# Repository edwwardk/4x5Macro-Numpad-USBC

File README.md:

## 4x5Macro-Numpad-USBC
This fork of tobychui's 4x5Macro-Numpad modifies the original design to use usbc instead of microusb as well as using a through hole reinforced port for a stronger hold on the board. Additionally, it also moves the user led to the front of the board and adds a button for resetting the mcu. Pins are identical to the 4x5Macro-Numpad to allow for using the same firmwares.

## v1.0 Known Issues
- resistor/capacitor/led designators/value missing from silkscreen in gerbers
- switch indices missing from silkscreen in gerbers
- size is larger than 100x100mm which causes upcharge (at least from jlcpcb)

### Bill of materials
(LCSC manufacturer part numbers in brackets)
- 1x CH552G (CH552G)
- 1x USBC (GT-USB-7010ASV)
- 20x switches for 4x5 layout, 17x switches for numpad layout
- 2x 0.1u 0805 capacitors (0805B104J250CT)
- 2x 0805 LEDs (17-215SURC/S530-A3/4T and BL-HJC35A-AV-TRB)
- 8x 10k 0805 resistors (SCR0805F10K)
- 2x 5.1k 0805 resistors (CR0805J80512G)
- 2x smd momentary buttons (TS5216A 250gf 025)

### Fabrication instructions
- in the "4x5Macro-Numpad-USBC/fabrication" folder there is a zip file called fabrication.zip. these are the set of gerbers required to order from JLCPCB and should work as is.

### Build Instruction

1. Send the PCB to print (See /PCB)

2. Purchase all the required materials (See BOM list)

3. 3D print the base plate (See /3D Model)

4. Install the required Arduino library for CH552G and drivers

5. Visit [4-key Macropad | imuslab](https://tobychui.github.io/4xMacropad/) (4xMacropad only) or modify the sketch in /firmware folder

6. Flash the CH552G with the sketch

### Program Flashing Instructions

As all the keyboard designs share the same MCU and programming button design, this instruction should be suitable for all the macropads / numpad in this repo.

1. Hold and press the PROG button on the PCB

2. While the button has been held, insert the USB cable into the mini USB port

3. Release the button when the Arduino code has finished compiling and ready to upload (Timing is important)

4. Wait for the upload to complete

### License

Software: MIT License

Hardware: CC BY-NC-SA

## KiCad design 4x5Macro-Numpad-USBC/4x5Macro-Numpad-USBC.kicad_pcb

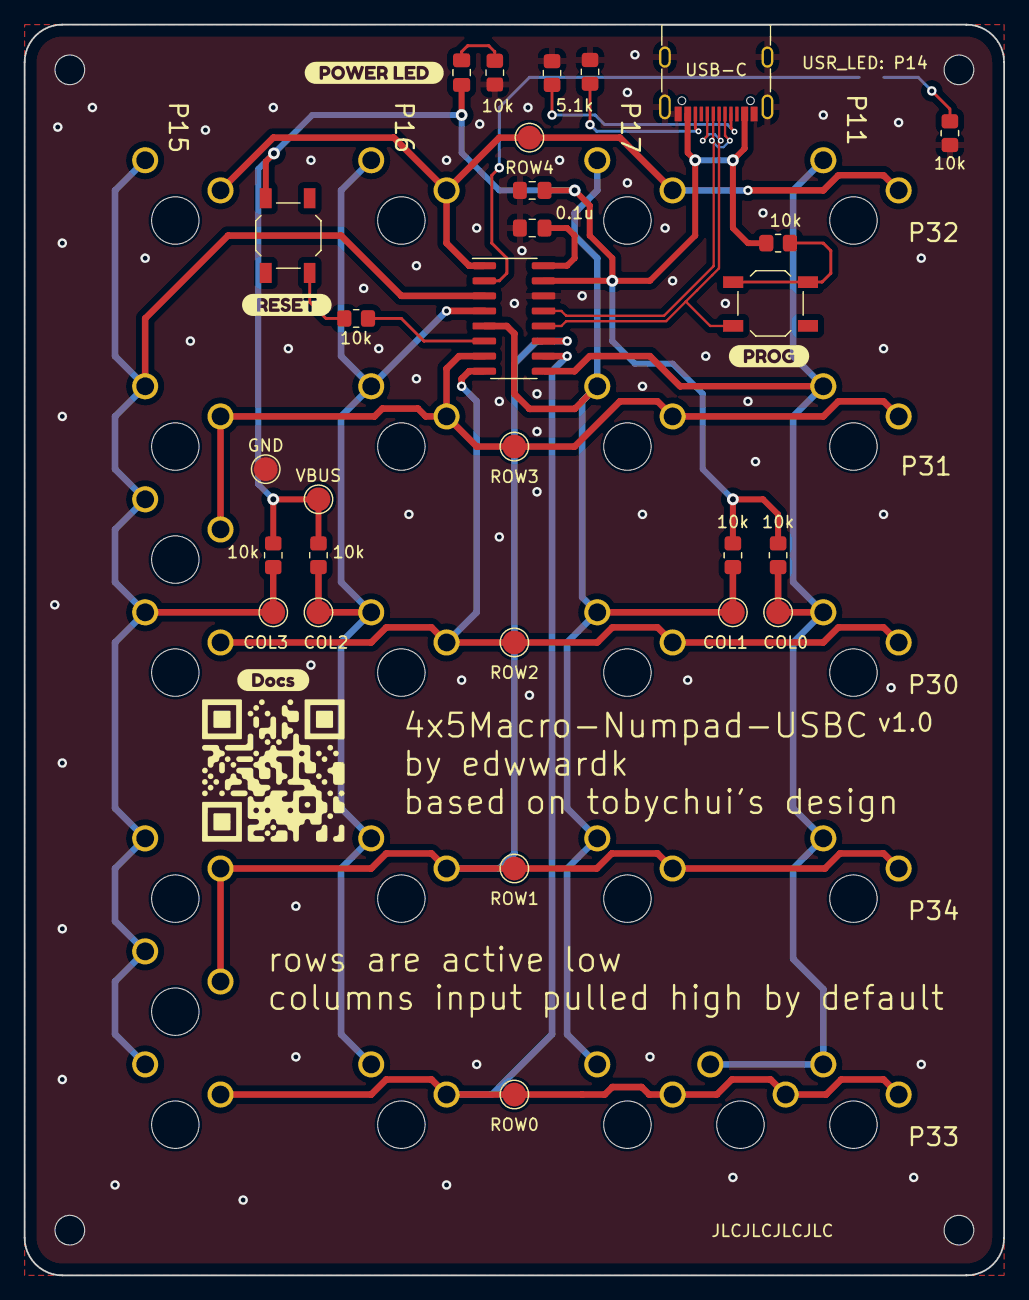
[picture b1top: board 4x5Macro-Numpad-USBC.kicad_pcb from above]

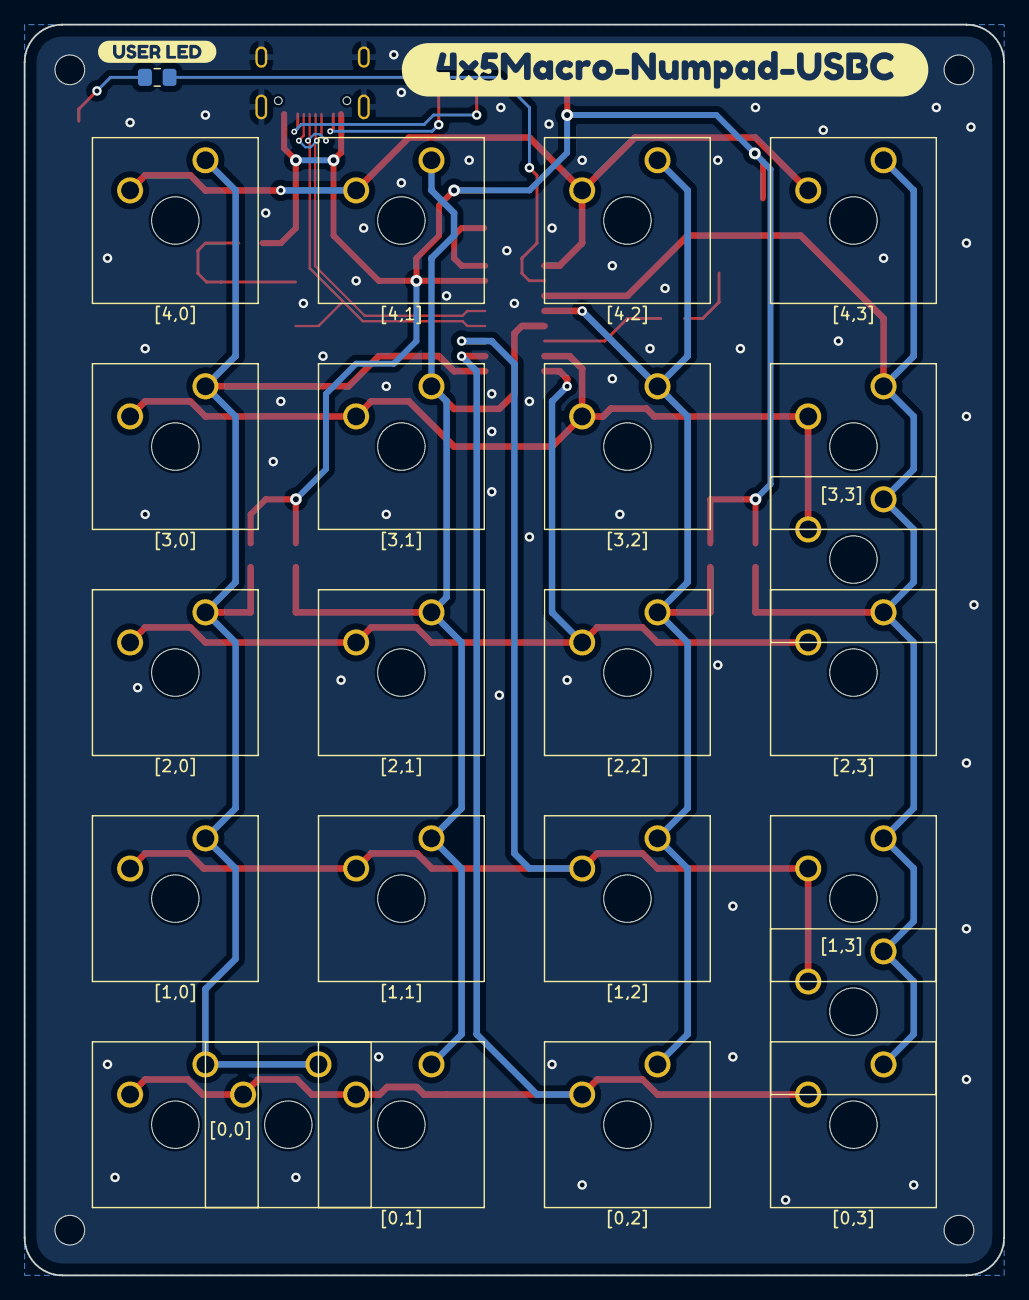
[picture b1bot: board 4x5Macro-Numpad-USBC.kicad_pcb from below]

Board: 2 copper layers, 82.5 x 105.4 mm, 62 parts (26 on the bottom side), 22 nets.

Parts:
C1, C2: 0.1u; C_0805_2012Metric_Pad1.18x1.45mm_HandSolder
CH1, CH1#2, CH1#3, CH1#4: MountingHole_2.5mm
COL0, COL1, COL2, COL3: TestPoint_Pad_D2.0mm
D1: RED; C_0805_2012Metric_Pad1.18x1.45mm_HandSolder
D2: BLUE; C_0805_2012Metric_Pad1.18x1.45mm_HandSolder
GND: TestPoint_Pad_D2.0mm
J1: USB-C; USB_C_Receptacle_G-Switch_GT-USB-7010ASV
R1, R4, R5, R6, R7, R8, R9, R10: 10k; R_0805_2012Metric_Pad1.20x1.40mm_HandSolder
R2, R3: 5.1k; R_0805_2012Metric_Pad1.20x1.40mm_HandSolder
ROW0, ROW1, ROW2, ROW3, ROW4: TestPoint_Pad_D2.0mm
SW1: PROG; SW_SPST_TS5216A
SW2: RESET; SW_SPST_TS5216A
SW3: [4,0]; SW_Cherry_MX_1.00u_Plate
SW4: [4,1]; SW_Cherry_MX_1.00u_Plate
SW5: [4,2]; SW_Cherry_MX_1.00u_Plate
SW6: [4,3]; SW_Cherry_MX_1.00u_Plate
SW7, SW11: [3,3]; SW_Cherry_MX_1.00u_Plate
SW8: [3,0]; SW_Cherry_MX_1.00u_Plate
SW9: [3,1]; SW_Cherry_MX_1.00u_Plate
SW10: [3,2]; SW_Cherry_MX_1.00u_Plate
SW12: [2,0]; SW_Cherry_MX_1.00u_Plate
SW13: [2,1]; SW_Cherry_MX_1.00u_Plate
SW14: [2,2]; SW_Cherry_MX_1.00u_Plate
SW15: [2,3]; SW_Cherry_MX_1.00u_Plate
SW16, SW20: [1,3]; SW_Cherry_MX_1.00u_Plate
SW17: [1,0]; SW_Cherry_MX_1.00u_Plate
SW18: [1,1]; SW_Cherry_MX_1.00u_Plate
SW19: [1,2]; SW_Cherry_MX_1.00u_Plate
SW21, SW25: [0,0]; SW_Cherry_MX_1.00u_Plate
SW22: [0,1]; SW_Cherry_MX_1.00u_Plate
SW23: [0,2]; SW_Cherry_MX_1.00u_Plate
SW24: [0,3]; SW_Cherry_MX_1.00u_Plate
U1: SOP-16_3.9x9.9mm_P1.27mm
VBUS: TestPoint_Pad_D2.0mm
kibuzzard-64E3BE21: G***; kibuzzard-64E3BE21
kibuzzard-64E3BEC4: G***; kibuzzard-64E3BEC4
kibuzzard-64E425AB: G***; kibuzzard-64E425AB
kibuzzard-64E425E5: G***; kibuzzard-64E425E5
kibuzzard-64E562F3: G***; kibuzzard-64E562F3
kibuzzard-64E42557: G***; kibuzzard-64E42557

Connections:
/USR_LED: D2.2 (A), U1.2 (P1.4)
COL0: COL0.1, R7.1, SW3.1, SW8.1, SW12.1, SW17.1, SW21.1, SW25.1, U1.9 (P1.1)
COL1: COL1.1, R8.1, SW4.1, SW9.1, SW13.1, SW18.1, SW22.1, U1.5 (P1.7)
COL2: COL2.1, R9.1, SW5.1, SW10.1, SW14.1, SW19.1, SW23.1, U1.4 (P1.6)
COL3: COL3.1, R10.1, SW6.1, SW7.1, SW11.1, SW15.1, SW16.1, SW20.1, SW24.1, U1.3 (P1.5)
D+: J1.A6 (D+), J1.B6 (D+), SW1.1, U1.12 (D+/PROG)
D-: J1.A7 (D-), J1.B7 (D-), U1.13 (D-)
GND: C1.1, C2.2, GND.1, J1.A1 (GND), J1.A12 (GND), J1.B1 (GND), J1.B12 (GND), J1.S1 (SHIELD), R2.2, R3.2, R4.2, R6.2, U1.14 (VSS)
unnamed: D1.1 (K), R4.1
unnamed: D2.1 (K), R6.1
unnamed: J1.A5 (CC1), R2.1
unnamed: J1.B5 (CC2), R3.1
unnamed: R1.1, SW1.2
unnamed: R5.1, SW2.2
unnamed: C1.2, U1.16 (CAP)
unnamed: R5.2, U1.6 (RST)
ROW0: ROW0.1, SW21.2, SW22.2, SW23.2, SW24.2, SW25.2, U1.10 (P3.3)
ROW1: ROW1.1, SW16.2, SW17.2, SW18.2, SW19.2, SW20.2, U1.11 (P3.4)
ROW2: ROW2.1, SW12.2, SW13.2, SW14.2, SW15.2, U1.8 (P3.0)
ROW3: ROW3.1, SW7.2, SW8.2, SW9.2, SW10.2, SW11.2, U1.7 (P3.1)
ROW4: ROW4.1, SW3.2, SW4.2, SW5.2, SW6.2, U1.1 (P3.2)
VBUS: C2.1, D1.2 (A), J1.A4 (VBUS), J1.A9 (VBUS), J1.B4 (VBUS), J1.B9 (VBUS), R1.2, R7.2, R8.2, R9.2, R10.2, SW2.1, U1.15 (VDD), VBUS.1

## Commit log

2023-08-21 sch done, footprints in, switches arranged
2023-08-22 fin+check sch, route pcb, silkscreen todo
2023-08-23 mask done, first board revision
2023-08-24 board vers 1.0
2023-10-22 delete
2023-10-24 start cad files
2023-10-25 basic case, mounting holes fixed, 3d models
